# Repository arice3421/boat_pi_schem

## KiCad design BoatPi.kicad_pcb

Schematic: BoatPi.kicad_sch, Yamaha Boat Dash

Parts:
C1: C_Polarized_Small_US; C_0805_2012Metric
C2, C6: C1812W104KDRACTU; CAPC4532X185N
C5: JMK316BBJ227ML-TE; CAPC3216X190N; PARTREV NA
C7, C8: C2012X5R1V106M125AC; CAPC2012X145N
C9: 10uf; C_0805_2012Metric
C25, C29: 100nF; C_0805_2012Metric
C26, C27, C28: 22pF_NM; C_0805_2012Metric
D2: ESDA6V1W5; SOT65P210X110-5N; PARTREV 2
D3: TVS-bidirectional Diode; D_0805_2012Metric
F1: 3550-2; FUSE_3550-2; PARTREV B
F2: 2A; Fuse_0805_2012Metric
Fuel_ADS1115: ADS1115BQDGSRQ1; SOP50P490X110-10N; PARTREV D
J1, J8: 1432431; Manufacturer_Part_Number 1432431; Mouser Part Number 651-1432431
J2, J6, J7: 1436987; Manufacturer_Part_Number 1436987; Mouser Part Number 651-1436987
J4: JAE_SIM_Card_SF72S006
J9: Micro_SD_Card_Det2; SDCARD_MOLEX_503398-1892
J10, J11, J12: CONSMA002-SMD-G; TE_CONSMA002-SMD-G; PARTREV D
J14: Barrel_Jack_MountingPin; BarrelJack_CUI_PJ-063AH_Horizontal
K1: Relay_SPDT; Relay_SPDT_Finder_36.11
L2: L; L_0805_2012Metric
M2: Fan_CPU_4pin; FanPinHeader_1x04_P2.54mm_Vertical
Module1: ComputeModule5-CM5; Raspberry-Pi-5-Compute-Module
NMEA2000_CanController2: MCP2562FD-H/SN; SOIC8-N_MC_MCH
PS1: RPL-10-CT; CONV_RPL-10-CT; PARTREV PRELIMINARY
Q2: BC107; TO-18-3
R1, R4, R6, R8, R10, R12, R14, R16: R1.2k; R_0805_2012Metric
R2, R3, R5, R7, R9, R11, R13, R15: R4.7k; R_0805_2012Metric
R17: 270Ohm; R_0805_2012Metric
R18, R19, R35: 470R; R_0805_2012Metric
R20: 7500; R_0805_2012Metric
R21: 1020; R_0805_2012Metric
R22: 100k; R_0805_2012Metric
R23: 12k; R_0805_2012Metric
R29, R30, R31: 22 Ohm; R_0805_2012Metric
R32: 0 Ohm; R_0805_2012Metric
R33: 4.7K; R_0805_2012Metric
R34: 47k; R_0805_2012Metric
U1: SIM7600E-H; IC_SIM7600E-H; M_PART_NUMBER SIM7600E-H
U2, U3, U4, U5, U6, U7, U8, U9: PC817; DIP-4_W7.62mm
U10: MIC29302AWU; TO-263-5_TabPin3
U11: RT9742BGJ5F; TSOT-23-5
U16: SC0917; MODULE_SC0917; PARTREV 1.9

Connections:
+3.3V: Fuel_ADS1115.8 (VDD), J6.3, Module1.78 (GPIO_VREF(1.8v/3.3v_Input)), Module1.84 (+3.3v_(Output)), Module1.86 (+3.3v_(Output)), R2.1, R3.1, R5.1, R7.1, R9.1, R11.1, R13.1, R15.1, R17.2, R23.1, U11.5 (VIN)
+5V: C5.1, C6.2, F2.1, M2.2 (+), Module1.77 (+5v_(Input)), NMEA2000_CanController2.3 (VDD), PS1.1_2 (VOUT), PS1.6_7 (VOUT), PS1.25 (SENSE), R21.1, U1.11 (USB_VBUS), U16.39 (VSYS); also elsewhere on the board
/CAN+: J1.3, NMEA2000_CanController2.6 (CANL)
/CAN-: J1.2, NMEA2000_CanController2.7 (CANH)
GND: C1.2, C2.2, C5.2, C7.2, C8.2, C9.2, C25.1, C26.1, C27.1, C28.1, C29.1, D2.2, D3.1 (K), Fuel_ADS1115.3 (GND), J1.1, J1.5, J1.MH1, J4.C5 (GND), J4.SH, J6.4, J6.5, J8.1, J9.6 (VSS), J9.11 (SHIELD), J10.2, J10.3, J11.2, J11.3, J12.2, J12.3, J14.2, K1.A2, M2.1 (-), Module1.1 (GND), Module1.2 (GND), Module1.7 (GND), Module1.8 (GND), Module1.13 (GND), Module1.14 (GND), Module1.22 (GND), Module1.23 (GND), Module1.32 (GND), Module1.33 (GND), Module1.42 (GND), Module1.43 (GND), Module1.52 (GND), Module1.53 (GND), Module1.59 (GND), Module1.60 (GND), Module1.65 (GND), Module1.66 (GND), Module1.71 (GND), Module1.74 (GND), Module1.98 (GND), NMEA2000_CanController2.2 (VSS), NMEA2000_CanController2.8 (STBY), PS1.10_11 (PGND), PS1.12 (PGND), PS1.18 (AGND), PS1.21 (AGND), Q2.1 (E), R18.2, R19.2, R20.2, R32.1, R34.1, U1.1 (GND), U1.2 (GND), U1.5 (GND), U1.10 (GND), U1.14 (GND), U1.37 (GND), U1.40 (GND), U1.41 (GND), U1.43 (GND), U1.57 (GND), U1.58 (GND), U1.60 (GND), U1.61 (GND), U1.64 (GND), U1.65 (GND), U1.77 (GND), U1.78 (GND), U1.80 (GND), U1.81 (GND), U2.3, U3.3, U4.3, U5.3, U6.3, U7.3, U8.3, U9.3, U10.3 (GND), U11.2 (GND), U16.3 (GND), U16.8 (GND), U16.13 (GND), U16.18 (GND), U16.23 (GND), U16.28 (GND), U16.33 (AGND), U16.38 (GND), U16.A (USB_SHIELD), U16.B (USB_SHIELD), U16.C (USB_SHIELD), U16.D (USB_SHIELD), U16.D2 (GND); also elsewhere on the board
GPIO2: Fuel_ADS1115.9 (SDA), Module1.58 (GPIO2)
GPIO3: Fuel_ADS1115.10 (SCL), Module1.56 (GPIO3)
GPIO8: J6.8, Module1.39 (GPIO8)
GPIO24: J6.6, Module1.45 (GPIO24)
GPIO25: J6.7, Module1.41 (GPIO25)
unnamed: C29.2, D3.2 (A), Q2.3 (C), U1.4 (RESET)
unnamed: F1.1_1, F1.1_2, J14.1
unnamed: F1.2_1, F1.2_2, J6.1, K1.11
unnamed: Fuel_ADS1115.4 (AIN0), J8.3, R17.1
unnamed: J2.1, R8.2
unnamed: J2.3, U2.2, U3.2, U4.2, U5.2
unnamed: J2.4, R1.2
unnamed: J2.5, R4.2
unnamed: J2.6, R6.2
unnamed: D2.4, J4.C3 (CLK), R30.2
unnamed: D2.5, J4.C7 (I/O), R29.2
unnamed: D2.3, J4.C2 (RST), R31.2
unnamed: C25.2, D2.1, J4.C1 (VCC), U1.20 (USIM_VDD)
unnamed: J6.2, K1.A1
unnamed: J7.1, R10.2
unnamed: J7.3, U6.2, U7.2, U8.2, U9.2
unnamed: J7.4, R12.2
unnamed: J7.5, R14.2
unnamed: J7.6, R16.2
unnamed: J9.5 (CLK), Module1.57 (SD_CLK)
unnamed: J9.3 (CMD), Module1.62 (SD_CMD)
unnamed: J9.7 (DAT0), Module1.63 (SD_DAT0)
unnamed: J9.8 (DAT1), Module1.67 (SD_DAT1)
unnamed: J9.1 (DAT2), Module1.69 (SD_DAT2)
unnamed: J9.2 (DAT3/CD), Module1.61 (SD_DAT3)
unnamed: C9.1, J9.4 (VDD), U11.1 (VOUT)
unnamed: L2.1, PS1.14_15 (SW), PS1.16 (SW), PS1.19_20 (SW), PS1.29 (SW)
unnamed: M2.4 (PWM), Module1.19 (FAN_PWM)
unnamed: M2.3 (Tacho), Module1.16 (FAN_TACHO)
unnamed: Module1.31 (GPIO12), R11.2, U7.4
unnamed: Module1.28 (GPIO13), R13.2, U8.4
unnamed: Module1.55 (GPIO14), U16.12 (GP9)
unnamed: Module1.51 (GPIO15), U16.11 (GP8)
unnamed: Module1.26 (GPIO19), R15.2, U9.4
unnamed: Module1.27 (GPIO20), R33.2
unnamed: Module1.46 (GPIO22), R3.2, U3.4
unnamed: Module1.47 (GPIO23), R5.2, U4.4
unnamed: Module1.48 (GPIO27), R2.2, U2.4
unnamed: Module1.75 (SD_PWR_ON), R23.2, U11.4 (~EN)
unnamed: NMEA2000_CanController2.4 (RXD), U16.29 (GP22)
unnamed: NMEA2000_CanController2.1 (TXD), U16.27 (GP21)
unnamed: C7.1, C8.1, J1.4, K1.14, PS1.3 (CTRL/UVLO), PS1.5 (+VIN), PS1.8 (+VIN), PS1.9 (+VIN), PS1.27 (+VIN), PS1.28 (+VIN)
unnamed: PS1.26 (FB), R20.1, R21.2
unnamed: PS1.4 (PG), R22.2
unnamed: C6.1, PS1.24 (SEQ)
unnamed: PS1.13 (VCC), R22.1
unnamed: Q2.2 (B), R33.1, R34.2
unnamed: R1.1, U2.1
unnamed: R4.1, U3.1
unnamed: R6.1, U4.1
unnamed: R8.1, U5.1
unnamed: R10.1, U6.1
unnamed: R12.1, U7.1
unnamed: R14.1, U8.1
unnamed: R16.1, U9.1
unnamed: J12.1, U1.59 (AUX_ANT)
unnamed: J10.1, U1.79 (GNSS_ANT)
unnamed: J11.1, U1.82 (MAIN_ANT)
unnamed: R32.2, U1.3 (PWRKEY)
unnamed: C27.2, R30.1, U1.19 (USIM_CLK)
unnamed: C26.2, R29.1, U1.17 (USIM_DATA)
unnamed: J4.CSW, J4.DSW, U1.53 (USIM_DET)
unnamed: C28.2, R31.1, U1.18 (USIM_RST)
unnamed: R19.1, R35.2, U10.5 (ADJ)
unnamed: F2.2, U10.1 (EN), U10.2 (VIN)
unnamed: C1.1, C2.1, R18.1, R35.1, U1.38 (VBAT), U1.39 (VBAT), U1.62 (VBAT), U1.63 (VBAT), U10.4 (VOUT)
unnamed: R7.2, U5.4, U16.1 (GP0)
unnamed: R9.2, U6.4, U16.2 (GP1)
USB_DN: U1.12 (USB_DN); also elsewhere on the board
USB_DP: U1.13 (USB_DP); also elsewhere on the board

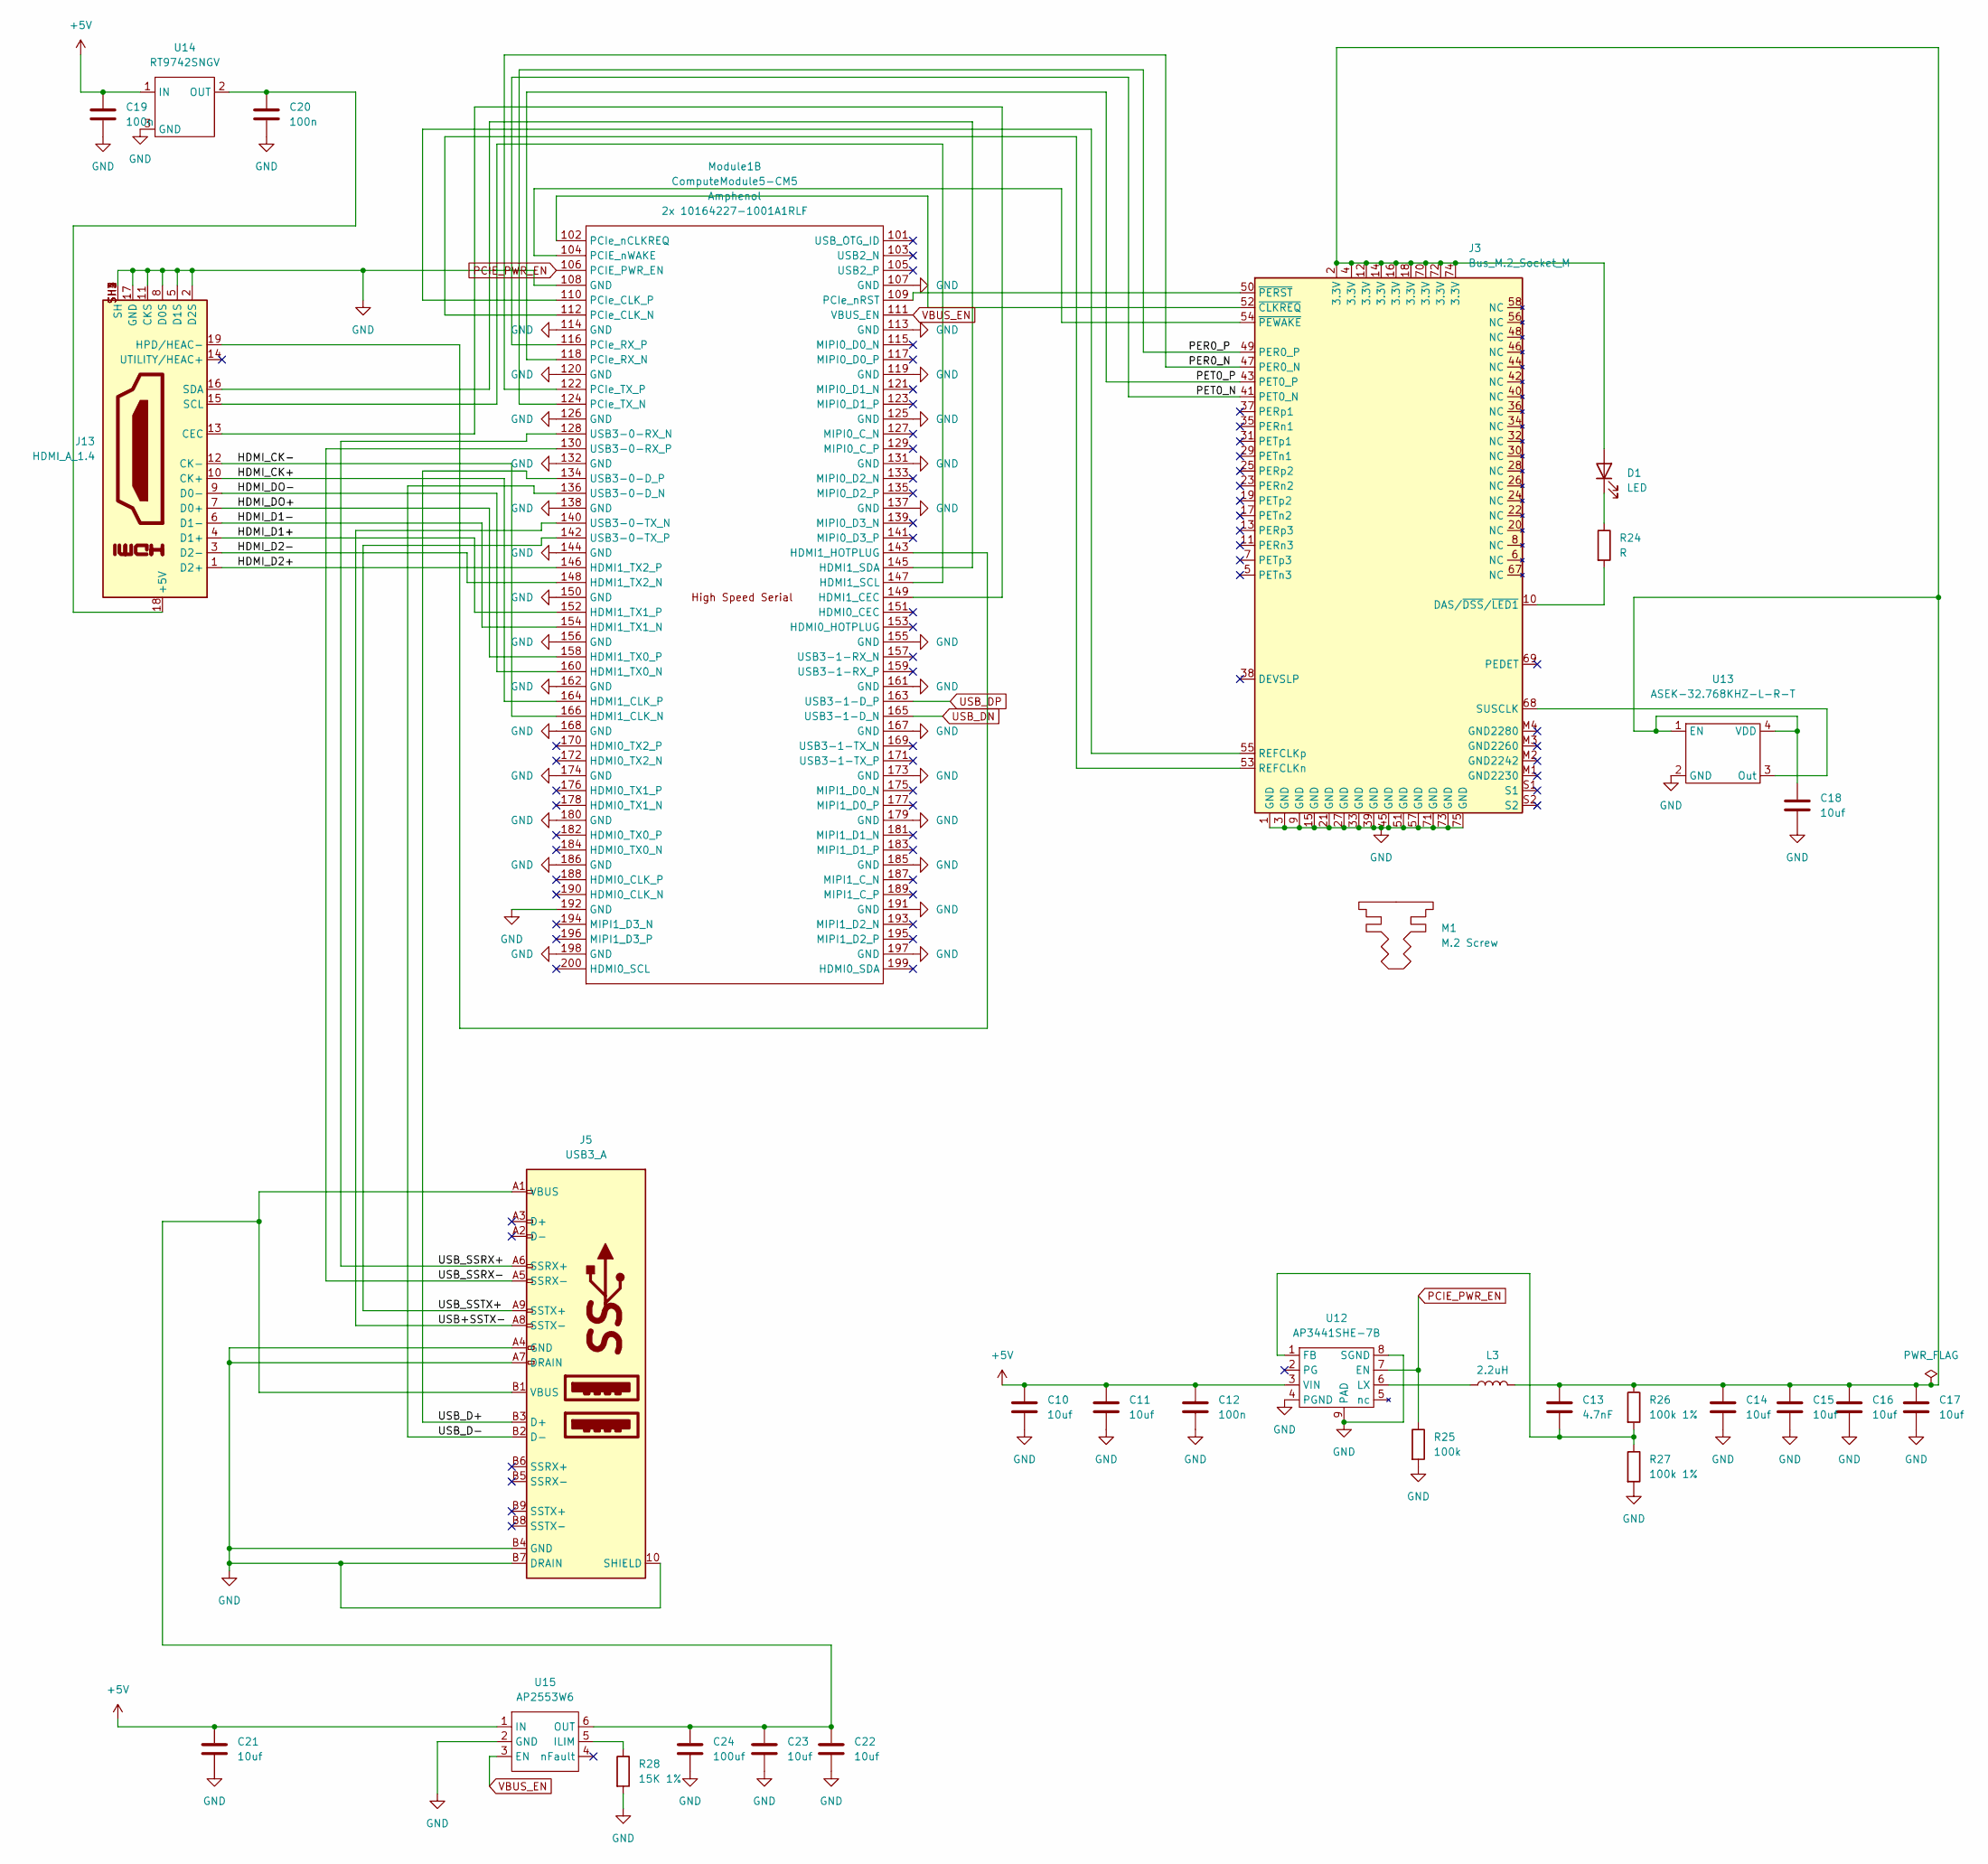
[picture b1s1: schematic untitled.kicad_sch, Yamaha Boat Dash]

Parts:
C10, C11, C14, C15, C16, C17, C18, C21, C22, C23: 10uf; C_0805_2012Metric
C12, C19, C20: 100n; C_0805_2012Metric
C13: 4.7nF; C_0805_2012Metric
C24: 100uf; C_0805_2012Metric
D1: LED; LED_0805_2012Metric
J3: Bus_M.2_Socket_M; M.2 M Key socket
J5: USB3_A; MTCONN_UBAF30-D2011
J13: HDMI_A_1.4; EDAC 690-019-298-412
L3: 2.2uH; L_0805_2012Metric
M1: M.2 Screw
Module1: ComputeModule5-CM5; Raspberry-Pi-5-Compute-Module
R24: R; R_0805_2012Metric
R25: 100k; R_0805_2012Metric
R26, R27: 100k 1%; R_0805_2012Metric
R28: 15K 1%; R_0805_2012Metric
U12: AP3441SHE-7B; DFN-8-1EP_3x3mm_P0.65mm_EP1.7x2.05mm
U13: ASEK-32.768KHZ-L-R-T; Crystal_SMD_3225-4Pin_3.2x2.5mm_HandSoldering
U14: RT9742SNGV; TSOT-23_HandSoldering
U15: AP2553W6; SOT-23-6_Handsoldering

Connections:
+5V: C10.1, C11.1, C12.1, C19.1, C21.1, U12.3 (VIN), U14.1 (IN), U15.1 (IN); also elsewhere on the board
/Sheet2/HDMI_CK+: J13.10 (CK+), Module1.164 (HDMI1_CLK_P)
/Sheet2/HDMI_CK-: J13.12 (CK-), Module1.166 (HDMI1_CLK_N)
/Sheet2/HDMI_D1+: J13.4 (D1+), Module1.152 (HDMI1_TX1_P)
/Sheet2/HDMI_D1-: J13.6 (D1-), Module1.154 (HDMI1_TX1_N)
/Sheet2/HDMI_D2+: J13.1 (D2+), Module1.146 (HDMI1_TX2_P)
/Sheet2/HDMI_D2-: J13.3 (D2-), Module1.148 (HDMI1_TX2_N)
/Sheet2/HDMI_DO+: J13.7 (D0+), Module1.158 (HDMI1_TX0_P)
/Sheet2/HDMI_DO-: J13.9 (D0-), Module1.160 (HDMI1_TX0_N)
/Sheet2/PER0_N: J3.47 (PER0_N), Module1.122 (PCIe_TX_P)
/Sheet2/PER0_P: J3.49 (PER0_P), Module1.124 (PCIe_TX_N)
/Sheet2/PET0_N: J3.41 (PET0_N), Module1.116 (PCIe_RX_P)
/Sheet2/PET0_P: J3.43 (PET0_P), Module1.118 (PCIe_RX_N)
/Sheet2/USB+SSTX-: J5.A8 (SSTX-), Module1.140 (USB3-0-TX_N)
/Sheet2/USB_D+: J5.B3 (D+), Module1.134 (USB3-0-D_P)
/Sheet2/USB_D-: J5.B2 (D-), Module1.136 (USB3-0-D_N)
/Sheet2/USB_SSRX+: J5.A6 (SSRX+), Module1.128 (USB3-0-RX_N)
/Sheet2/USB_SSRX-: J5.A5 (SSRX-), Module1.130 (USB3-0-RX_P)
/Sheet2/USB_SSTX+: J5.A9 (SSTX+), Module1.142 (USB3-0-TX_P)
GND: C10.2, C11.2, C12.2, C14.2, C15.2, C16.2, C17.2, C18.2, C19.2, C20.2, C21.2, C22.2, C23.2, C24.2, J3.1 (GND), J3.3 (GND), J3.9 (GND), J3.15 (GND), J3.21 (GND), J3.27 (GND), J3.33 (GND), J3.39 (GND), J3.45 (GND), J3.51 (GND), J3.57 (GND), J3.71 (GND), J3.73 (GND), J3.75 (GND), J5.10 (SHIELD), J5.A4 (GND), J5.A7 (DRAIN), J5.B4 (GND), J5.B7 (DRAIN), J13.2 (D2S), J13.5 (D1S), J13.8 (D0S), J13.11 (CKS), J13.17 (GND), J13.SH1 (SH), J13.SH2 (SH), J13.SH3 (SH), J13.SH4 (SH), Module1.107 (GND), Module1.108 (GND), Module1.113 (GND), Module1.114 (GND), Module1.119 (GND), Module1.120 (GND), Module1.125 (GND), Module1.126 (GND), Module1.131 (GND), Module1.132 (GND), Module1.137 (GND), Module1.138 (GND), Module1.144 (GND), Module1.150 (GND), Module1.155 (GND), Module1.156 (GND), Module1.161 (GND), Module1.162 (GND), Module1.167 (GND), Module1.168 (GND), Module1.173 (GND), Module1.174 (GND), Module1.179 (GND), Module1.180 (GND), Module1.185 (GND), Module1.186 (GND), Module1.191 (GND), Module1.192 (GND), Module1.197 (GND), Module1.198 (GND), R25.2, R27.2, R28.2, U12.4 (PGND), U12.8 (SGND), U12.9 (PAD), U13.2 (GND), U14.3 (GND), U15.2 (GND); also elsewhere on the board
unnamed: C13.1, C14.1, C15.1, C16.1, C17.1, C18.1, D1.2 (A), J3.2 (3.3V), J3.4 (3.3V), J3.12 (3.3V), J3.14 (3.3V), J3.16 (3.3V), J3.18 (3.3V), J3.70 (3.3V), J3.72 (3.3V), J3.74 (3.3V), L3.2, R26.1, U13.1 (EN), U13.4 (VDD)
unnamed: D1.1 (K), R24.1
unnamed: J3.10 (DAS/~DSS/~LED1), R24.2
unnamed: J3.53 (REFCLKn), Module1.112 (PCIe_CLK_N)
unnamed: J3.55 (REFCLKp), Module1.110 (PCIe_CLK_P)
unnamed: J3.68 (SUSCLK), U13.3 (Out)
unnamed: J3.52 (~CLKREQ), Module1.102 (PCIe_nCLKREQ)
unnamed: J3.50 (~PERST), Module1.109 (PCIe_nRST)
unnamed: J3.54 (~PEWAKE), Module1.104 (PCIE_nWAKE)
unnamed: C20.1, J13.18 (+5V), U14.2 (OUT)
unnamed: J13.13 (CEC), Module1.149 (HDMI1_CEC)
unnamed: J13.19 (HPD/HEAC-), Module1.143 (HDMI1_HOTPLUG)
unnamed: J13.15 (SCL), Module1.147 (HDMI1_SCL)
unnamed: J13.16 (SDA), Module1.145 (HDMI1_SDA)
unnamed: C13.2, R26.2, R27.1, U12.1 (FB)
unnamed: L3.1, U12.6 (LX)
unnamed: R28.1, U15.5 (ILIM)
unnamed: C22.1, C23.1, C24.1, J5.A1 (VBUS), J5.B1 (VBUS), U15.6 (OUT)
PCIE_PWR_EN: Module1.106 (PCIE_PWR_EN), R25.1, U12.7 (EN)
USB_DN: Module1.165 (USB3-1-D_N); also elsewhere on the board
USB_DP: Module1.163 (USB3-1-D_P); also elsewhere on the board
VBUS_EN: Module1.111 (VBUS_EN), U15.3 (EN)

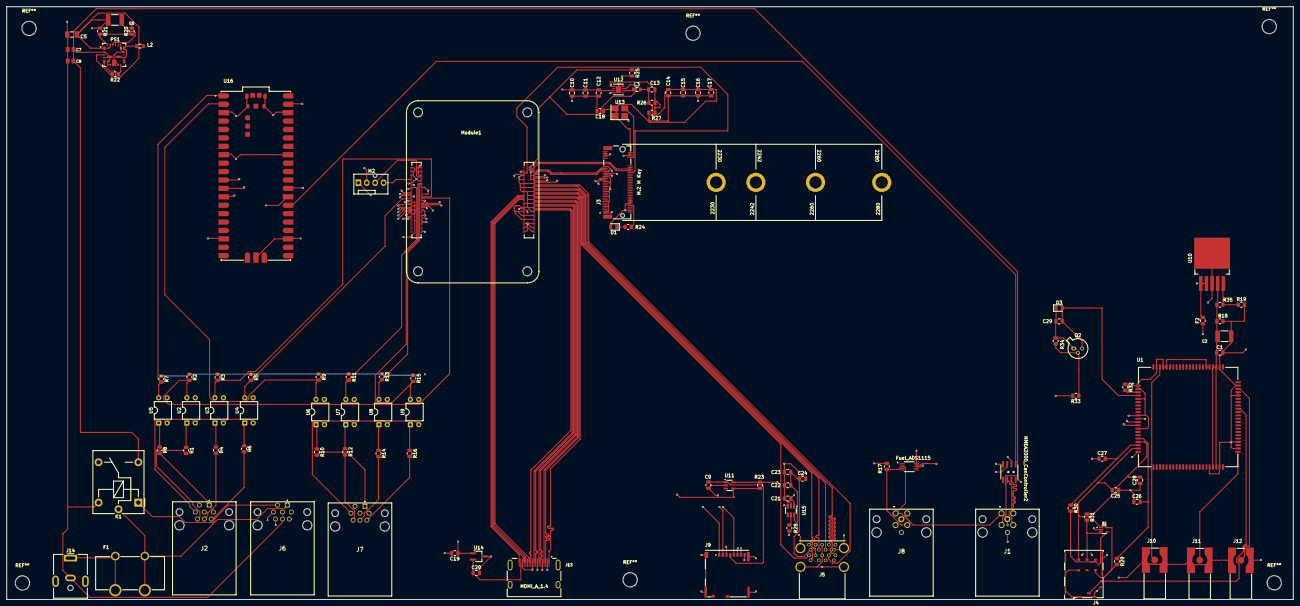
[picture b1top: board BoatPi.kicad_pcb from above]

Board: 6 copper layers, 388.5 x 179.0 mm, 106 parts (0 on the bottom side), 118 nets.

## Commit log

2025-08-27 Test Change
2025-08-27 New Test
2025-08-29 started PCB
2025-09-02 At home update
2025-09-02 Updated from work
2025-09-02 Fixed scheme
2025-09-03 Home push
2025-09-03 Work Changes and documentation
2025-09-03 Updated to CM5 Doc
2025-09-04 fixed stuff at home
2025-09-04 PCIE Changes
2025-09-05 diff pairs
2025-09-08 Fixes from datasheets
2025-09-08 Final Updates
2025-09-09 Label Fixes
